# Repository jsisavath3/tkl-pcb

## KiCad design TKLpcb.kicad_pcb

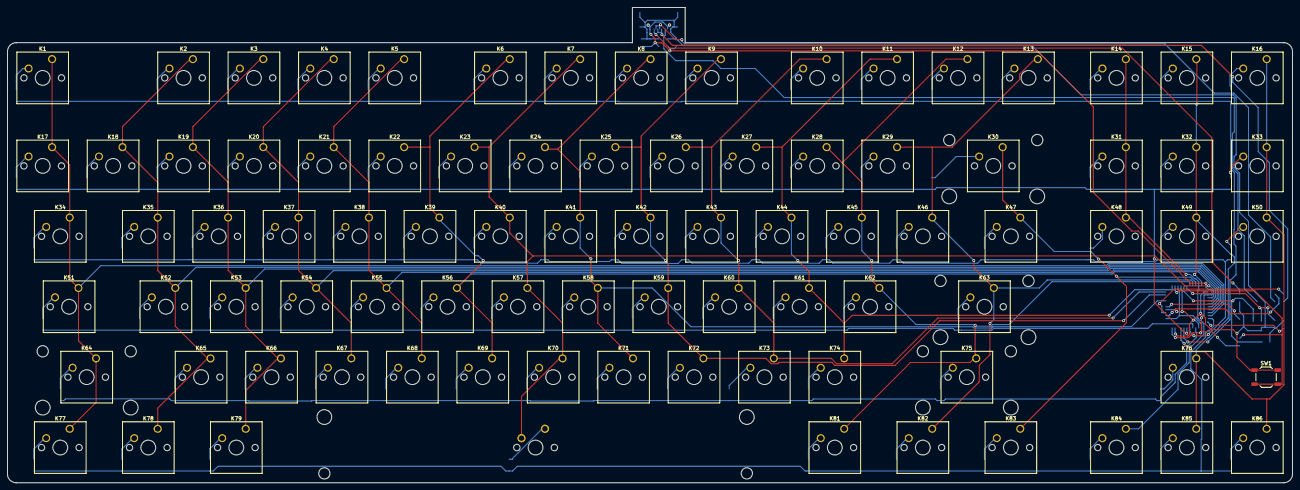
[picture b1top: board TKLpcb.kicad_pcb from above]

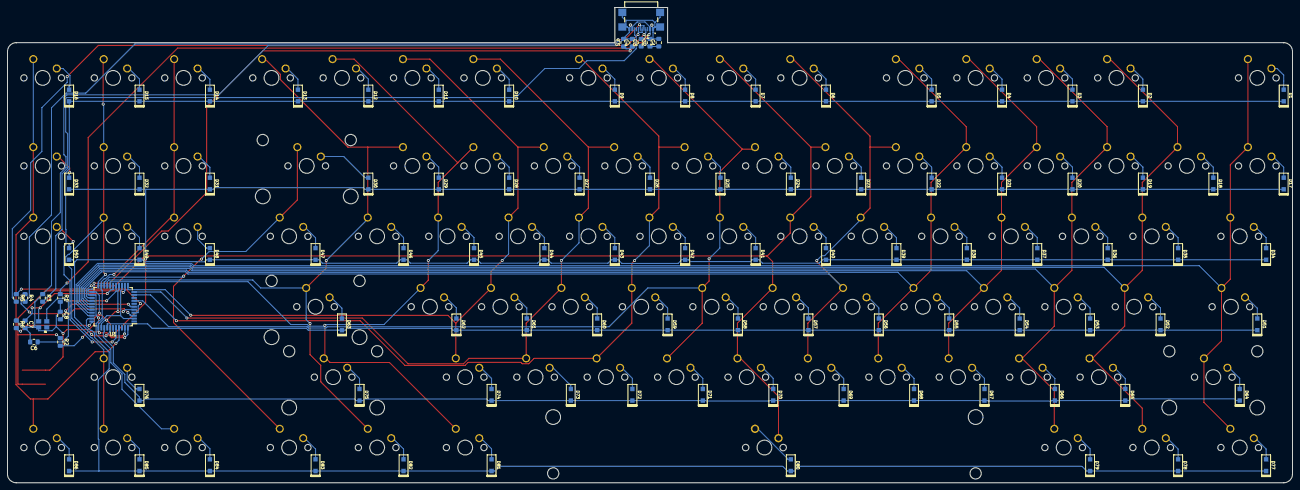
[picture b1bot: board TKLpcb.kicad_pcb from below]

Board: 2 copper layers, 347.7 x 128.6 mm, 190 parts (103 on the bottom side), 122 nets.

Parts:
C1, C2, C3, C4: 0.1u; C_0805_2012Metric_Pad1.15x1.40mm_HandSolder
C5: 4.7u; C_0805_2012Metric_Pad1.15x1.40mm_HandSolder
C6, C7: 22p; C_0805_2012Metric_Pad1.15x1.40mm_HandSolder
C8: 1u; C_0805_2012Metric_Pad1.15x1.40mm_HandSolder
D1, D2, D3, D4, D5, D6, D7, D8, D9, D10, D11, D12, D13, D14, D15, D16, D17, D18, D19, D20, D21, D22, D23, D24, D25, D26, D27, D28, D29, D30, D31, D32, D33, D34, D35, D36, D37, D38, D39, D40, D41, D42, D43, D44, D45, D46, D47, D48, D49, D50, D51, D52, D53, D54, D55, D56, D57, D58, D59, D60, D61, D62, D63, D64, D65, D66, D67, D68, D69, D70, D71, D72, D73, D74, D75, D76, D77, D78, D79, D80, D81, D82, D83, D84, D85, D86: D; D_SOD123_hand
J1: USB_C; GCT_USB4110-GF-A
K1, K2, K3, K4, K5, K6, K7, K8, K9, K10, K11, K12, K13, K14, K15, K16, K17, K18, K19, K20, K21, K22, K23, K24, K25, K26, K27, K28, K29, K31, K32, K33, K35, K36, K37, K38, K39, K40, K41, K42, K43, K44, K45, K46, K48, K49, K50, K52, K53, K54, K55, K56, K57, K58, K59, K60, K61, K62, K65, K66, K67, K68, K69, K70, K71, K72, K73, K74, K76, K78, K82, K84, K85, K86: KEYSW; SW_Cherry_MX_1.00u_PCB
K30: KEYSW; SW_Cherry_MX_2.00u_PCB
K34, K47, K77, K79, K81, K83: KEYSW; SW_Cherry_MX_1.50u_PCB
K51: KEYSW; SW_Cherry_MX_1.75u_PCB
K63, K64: KEYSW; SW_Cherry_MX_2.25u_PCB
K75: KEYSW; SW_Cherry_MX_2.75u_PCB
K80: KEYSW; MXOnly-7U-ReversedStabilizers-NoLED
R1, R3: 5.1k; R_0805_2012Metric_Pad1.15x1.40mm_HandSolder
R2, R6: 10k; R_0805_2012Metric_Pad1.15x1.40mm_HandSolder
R4, R5: 22; R_0805_2012Metric_Pad1.15x1.40mm_HandSolder
SW1: SW_PUSH; SW_SPST_TL3342
U1: ATMEGA32U4; TQFP-44_10x10mm_P0.8mm
X1: XTAL_GND; OSCCC320X250X70-4N

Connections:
/col0: K1.1, K17.1, K34.1, K51.1, K64.1, K77.1, U1.31
/col1: K2.1, K18.1, K35.1, K52.1, K65.1, K78.1, U1.30
/col2: K3.1, K19.1, K36.1, K53.1, K66.1, K79.1, U1.29
/col3: K4.1, K20.1, K37.1, K54.1, K67.1, U1.28
/col4: K5.1, K21.1, K38.1, K55.1, K68.1, U1.27
/col5: K6.1, K22.1, K39.1, K56.1, K69.1, U1.26
/col6: K7.1, K23.1, K40.1, K57.1, K70.1, K80.1, U1.25
/col7: K8.1, K24.1, K41.1, K58.1, K71.1, U1.8
/col9: K9.1, K25.1, K42.1, K59.1, K72.1, U1.10
/col10: K10.1, K26.1, K43.1, K60.1, K73.1, U1.11
/col11: K11.1, K27.1, K44.1, K61.1, K74.1, U1.12
/col12: K12.1, K28.1, K45.1, K62.1, K75.1, K81.1, U1.18
/col13: K13.1, K29.1, K46.1, K63.1, K82.1, U1.19
/col14: K30.1, K47.1, K83.1, U1.20
/col15: K14.1, K31.1, K48.1, K84.1, U1.21
/col16: K15.1, K32.1, K49.1, K76.1, K85.1, U1.22
/col17: K16.1, K33.1, K50.1, K86.1, U1.41
/dn: J1.A7, J1.B7, R4.2
/row0: D1.1, D2.1, D3.1, D4.1, D5.1, D6.1, D7.1, D8.1, D9.1, D10.1, D11.1, D12.1, D13.1, D14.1, D15.1, D16.1, U1.40
/row1: D17.1, D18.1, D19.1, D20.1, D21.1, D22.1, D23.1, D24.1, D25.1, D26.1, D27.1, D28.1, D29.1, D30.1, D31.1, D32.1, D33.1, U1.39
/row2: D34.1, D35.1, D36.1, D37.1, D38.1, D39.1, D40.1, D41.1, D42.1, D43.1, D44.1, D45.1, D46.1, D47.1, D48.1, D49.1, D50.1, U1.38
/row3: D51.1, D52.1, D53.1, D54.1, D55.1, D56.1, D57.1, D58.1, D59.1, D60.1, D61.1, D62.1, D63.1, U1.37
/row4: D64.1, D65.1, D66.1, D67.1, D68.1, D69.1, D70.1, D71.1, D72.1, D73.1, D74.1, D75.1, D76.1, U1.36
/row5: D77.1, D78.1, D79.1, D80.1, D81.1, D82.1, D83.1, D84.1, D85.1, D86.1, U1.32
GND: C1.2, C2.2, C3.2, C4.2, C5.2, C6.2, C7.2, C8.1, J1.A1/B12, J1.B1/A12, J1.S1, J1.S2, J1.S3, J1.S4, R1.2, R3.1, R6.1, SW1.1, U1.5, U1.15, U1.23, U1.35, U1.43, X1.3
unnamed: C6.1, U1.16, X1.1
unnamed: C7.1, U1.17, X1.2
unnamed: C8.2, U1.6
unnamed: D1.2, K1.2
unnamed: D2.2, K2.2
unnamed: D3.2, K3.2
unnamed: D4.2, K4.2
unnamed: D5.2, K5.2
unnamed: D6.2, K6.2
unnamed: D7.2, K7.2
unnamed: D8.2, K8.2
unnamed: D9.2, K9.2
unnamed: D10.2, K10.2
unnamed: D11.2, K11.2
unnamed: D12.2, K12.2
unnamed: D13.2, K13.2
unnamed: D14.2, K14.2
unnamed: D15.2, K15.2
unnamed: D16.2, K16.2
unnamed: D17.2, K17.2
unnamed: D18.2, K18.2
unnamed: D19.2, K19.2
unnamed: D20.2, K20.2
unnamed: D21.2, K21.2
unnamed: D22.2, K22.2
unnamed: D23.2, K23.2
unnamed: D24.2, K24.2
unnamed: D25.2, K25.2
unnamed: D26.2, K26.2
unnamed: D27.2, K27.2
unnamed: D28.2, K28.2
unnamed: D29.2, K29.2
unnamed: D30.2, K30.2
unnamed: D31.2, K31.2
unnamed: D32.2, K32.2
unnamed: D33.2, K33.2
unnamed: D34.2, K34.2
unnamed: D35.2, K35.2
unnamed: D36.2, K36.2
unnamed: D37.2, K37.2
unnamed: D38.2, K38.2
unnamed: D39.2, K39.2
unnamed: D40.2, K40.2
unnamed: D41.2, K41.2
unnamed: D42.2, K42.2
unnamed: D43.2, K43.2
unnamed: D44.2, K44.2
unnamed: D45.2, K45.2
unnamed: D46.2, K46.2
unnamed: D47.2, K47.2
unnamed: D48.2, K48.2
unnamed: D49.2, K49.2
unnamed: D50.2, K50.2
unnamed: D51.2, K51.2
unnamed: D52.2, K52.2
unnamed: D53.2, K53.2
unnamed: D54.2, K54.2
unnamed: D55.2, K55.2
unnamed: D56.2, K56.2
unnamed: D57.2, K57.2
unnamed: D58.2, K58.2
unnamed: D59.2, K59.2
unnamed: D60.2, K60.2
unnamed: D61.2, K61.2
unnamed: D62.2, K62.2
unnamed: D63.2, K63.2
unnamed: D64.2, K64.2
unnamed: D65.2, K65.2
unnamed: D66.2, K66.2
unnamed: D67.2, K67.2
unnamed: D68.2, K68.2
unnamed: D69.2, K69.2
unnamed: D70.2, K70.2
unnamed: D71.2, K71.2
unnamed: D72.2, K72.2
unnamed: D73.2, K73.2
unnamed: D74.2, K74.2
unnamed: D75.2, K75.2
unnamed: D76.2, K76.2
unnamed: D77.2, K77.2
unnamed: D78.2, K78.2
unnamed: D79.2, K79.2
unnamed: D80.2, K80.2
unnamed: D81.2, K81.2
unnamed: D82.2, K82.2
unnamed: D83.2, K83.2
unnamed: D84.2, K84.2
unnamed: D85.2, K85.2
unnamed: D86.2, K86.2
unnamed: J1.A5, R1.1
unnamed: J1.A6, J1.B6, R5.2
unnamed: J1.B5, R3.2
unnamed: R2.1, SW1.2, U1.13
unnamed: R4.1, U1.3
unnamed: R5.1, U1.4
unnamed: R6.2, U1.33
VCC: C1.1, C2.1, C3.1, C4.1, C5.1, J1.A4/B9, J1.B4/A9, R2.2, U1.2, U1.14, U1.24, U1.34, U1.44

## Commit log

2020-07-31 help
